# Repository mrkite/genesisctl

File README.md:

# Genesis Controller to JAMMA adapter

This is my circuit design to allow a genesis controller to be used in a JAMMA system without any hardware modifications to the controller.

The genesis controller interfaces over a DB9 connector.  There aren't enough pins to map all the buttons to pins, so it muxes two sets of buttons to the same pins.  A select pin changes which button states are returned depending on if it's tied to +5 or ground.

So this simple circuit toggles the select pin back and forth and latches each pin to a unique output.

## How it works

The `555` timer generates a 50% duty cycle square wave on pin 3.  The frequency, determined by the RC value, is very sensitive to the actual value of the resistors and capacitors.  So you will want to use an oscilloscope to measure the actual frequency.  As long as the frequency is at least 120 Hz the circuit will work without any lag.

The square wave is routed into the clock input of the `74ls74` JK Flip Flop.  You'll notice that the inverted output is routed into the input.  This means with every rising clock pulse, the output will invert.  The purpose of this chip is to give us two clock signals, one inverted, without any delay between the two.

There are two `74ls374` latches.  One uses the straight clock, the other uses the inverted clock.  This results in the two latches switching back and forth latching the data pins.

One of the clocks is also sent to the select pin.  Due to propagation delay, the latch fires on the rising edge of the clock before the select pin can be raised high.  Meaning latch using the clock sent to select will be latching the ground-state buttons while the other latch will be latching the active select buttons.

The board uses a simple 10-pin header which will allow you to easily crimp a
`DB9` jack to one end of a ribbon cable with a `2x5 IDC` socket on the other.

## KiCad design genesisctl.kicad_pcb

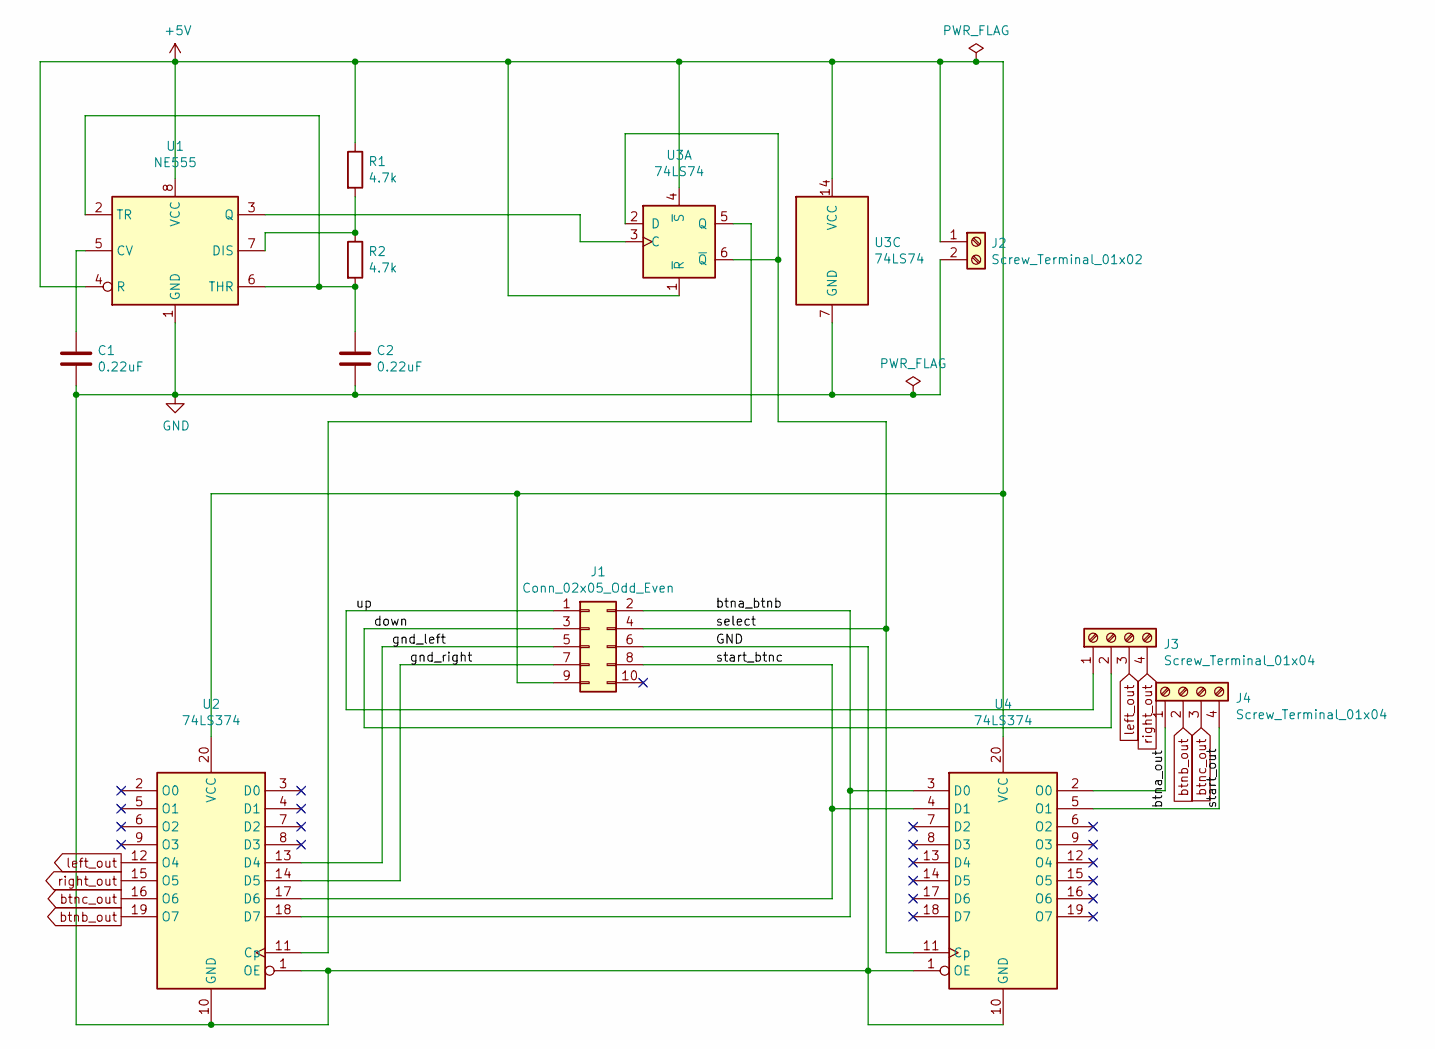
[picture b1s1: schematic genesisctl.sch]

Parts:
C1, C2: 0.22uF; CP_Radial_Tantal_D4.5mm_P5.00mm
J1: Conn_02x05_Odd_Even; PinHeader_2x05_P2.54mm_Vertical
J2: Screw_Terminal_01x02; TerminalBlock_MetzConnect_Type094_RT03502HBLU_1x02_P5.00mm_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
J3, J4: Screw_Terminal_01x04; TerminalBlock_MetzConnect_Type094_RT03504HBLU_1x04_P5.00mm_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
R1, R2: 4.7k; R_Axial_DIN0207_L6.3mm_D2.5mm_P7.62mm_Horizontal
U1: NE555; DIP-8_W7.62mm
U2, U4: 74LS374; DIP-20_W7.62mm
U3: 74LS74; DIP-14_W7.62mm

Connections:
+5V: J1.9, J2.1, R1.1, U1.4 (R), U1.8 (VCC), U2.20 (VCC), U3.1 (~R), U3.4 (~S), U3.14 (VCC), U4.20 (VCC)
/btna_btnb: J1.2, U2.18 (D7), U4.3 (D0)
/btna_out: J4.4, U4.5 (O1)
/down: J1.3, J3.2
/gnd_left: J1.5, U2.13 (D4)
/gnd_right: J1.7, U2.14 (D5)
/select: J1.4, U3.2 (D), U3.6 (~Q), U4.11 (Cp)
/start_btnc: J1.8, U2.17 (D6), U4.4 (D1)
/up: J1.1, J3.1
GND: C1.2, C2.2, J1.6, J2.2, U1.1 (GND), U2.1 (OE), U2.10 (GND), U3.7 (GND), U4.1 (OE), U4.10 (GND)
unnamed: C1.1, U1.5 (CV)
unnamed: C2.1, R2.2, U1.2 (TR), U1.6 (THR)
unnamed: J4.1, U4.2 (O0)
unnamed: R1.2, R2.1, U1.7 (DIS)
unnamed: U1.3 (Q), U3.3 (C)
unnamed: U2.11 (Cp), U3.5 (Q)
btnb_out: J4.2, U2.19 (O7)
btnc_out: J4.3, U2.16 (O6)
left_out: J3.3, U2.12 (O4)
right_out: J3.4, U2.15 (O5)

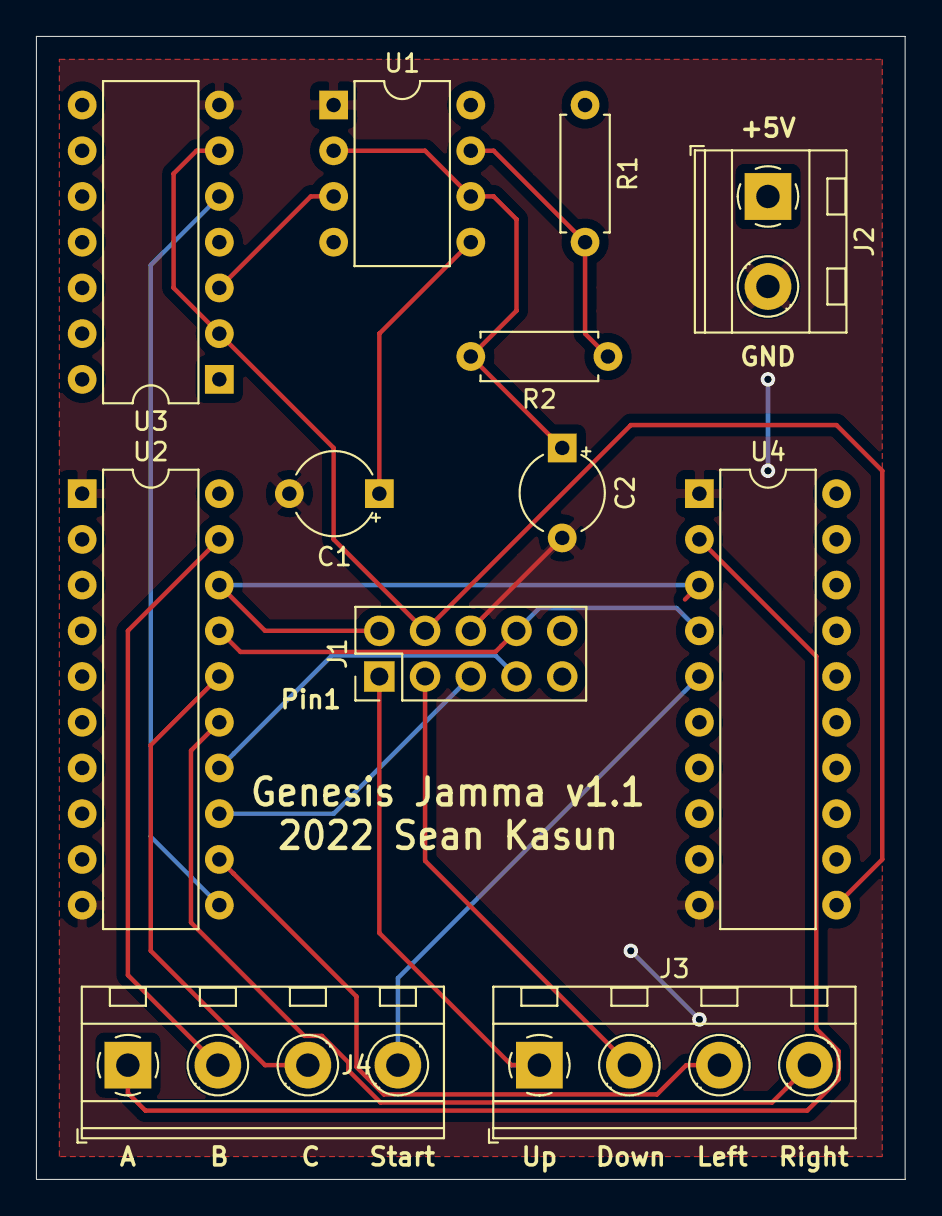
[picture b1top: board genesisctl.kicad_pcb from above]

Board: 2 copper layers, 48.3 x 63.5 mm, 12 parts (0 on the bottom side), 20 nets.

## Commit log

2021-12-03 initial import
2021-12-08 added gerber files
2022-01-19 fixed reversed left/right
2022-01-28 added images
